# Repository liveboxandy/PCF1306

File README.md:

# PCF1306 LBA Version
PCF1306 Replacement KiCAD Project

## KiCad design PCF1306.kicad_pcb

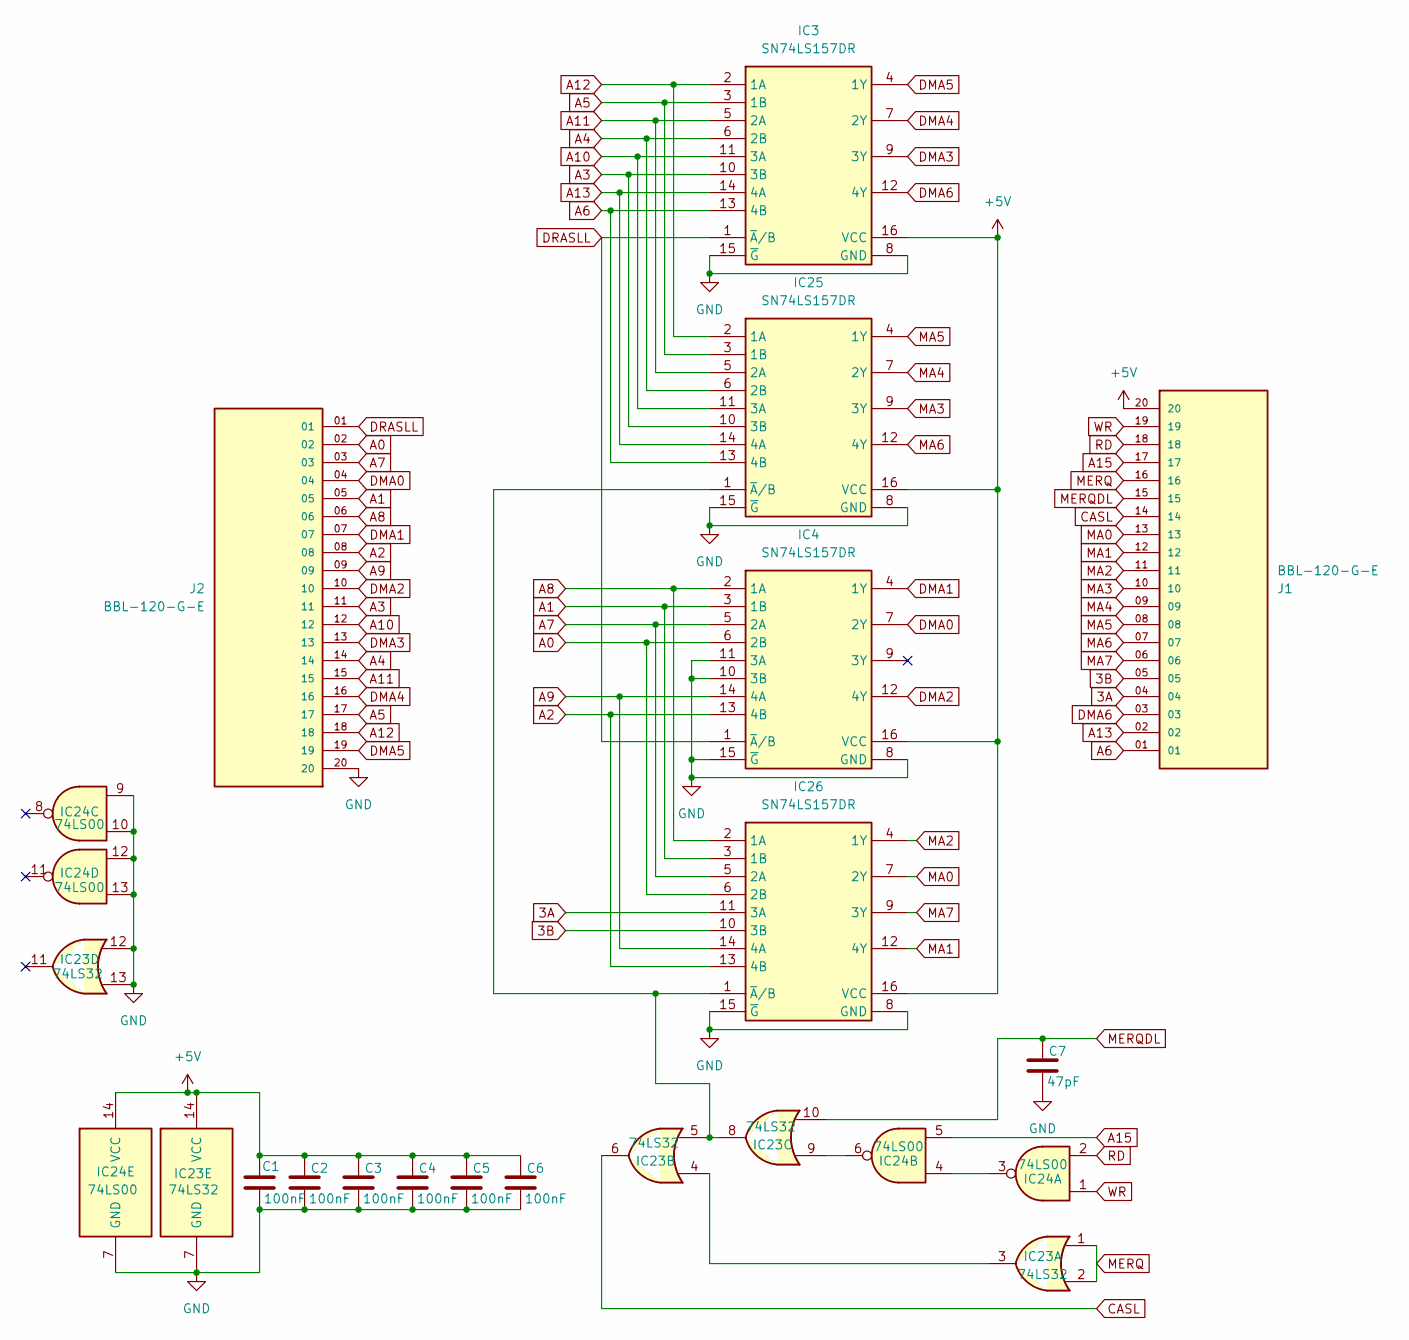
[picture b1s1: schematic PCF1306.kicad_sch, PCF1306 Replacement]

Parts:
C1, C2, C3, C4, C5, C6: 100nF; C_0805_2012Metric
C7: 47pF; C_0805_2012Metric
IC3, IC4, IC25, IC26: SN74LS157DR; SOIC127P600X175-16N; Mouser Part Number 595-SN74LS157DR
IC23: 74LS32; SOIC127P600X175-14N
IC24: 74LS00; SOIC127P600X175-14N
J1, J2: BBL-120-G-E; SAMTEC_BBL-120-G-E; PARTREV R

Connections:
3A: IC26.11 (3A), J1.04
3B: IC26.10 (3B), J1.05
+5V: C1.1, C2.1, C3.1, C4.1, C5.1, C6.1, IC3.16 (VCC), IC4.16 (VCC), IC23.14 (VCC), IC24.14 (VCC), IC25.16 (VCC), IC26.16 (VCC), J1.20
A0: IC4.6 (2B), IC26.6 (2B), J2.02
A1: IC4.3 (1B), IC26.3 (1B), J2.05
A2: IC4.13 (4B), IC26.13 (4B), J2.08
A3: IC3.10 (3B), IC25.10 (3B), J2.11
A4: IC3.6 (2B), IC25.6 (2B), J2.14
A5: IC3.3 (1B), IC25.3 (1B), J2.17
A6: IC3.13 (4B), IC25.13 (4B), J1.01
A7: IC4.5 (2A), IC26.5 (2A), J2.03
A8: IC4.2 (1A), IC26.2 (1A), J2.06
A9: IC4.14 (4A), IC26.14 (4A), J2.09
A10: IC3.11 (3A), IC25.11 (3A), J2.12
A11: IC3.5 (2A), IC25.5 (2A), J2.15
A12: IC3.2 (1A), IC25.2 (1A), J2.18
A13: IC3.14 (4A), IC25.14 (4A), J1.02
A15: IC24.5, J1.17
CASL: IC23.6, J1.14
DMA0: IC4.7 (2Y), J2.04
DMA1: IC4.4 (1Y), J2.07
DMA2: IC4.12 (4Y), J2.10
DMA3: IC3.9 (3Y), J2.13
DMA4: IC3.7 (2Y), J2.16
DMA5: IC3.4 (1Y), J2.19
DMA6: IC3.12 (4Y), J1.03
DRASLL: IC3.1 (~A/B), IC4.1 (~A/B), J2.01
GND: C1.2, C2.2, C3.2, C4.2, C5.2, C6.2, C7.2, IC3.8 (GND), IC3.15 (~G), IC4.8 (GND), IC4.10 (3B), IC4.11 (3A), IC4.15 (~G), IC23.7 (GND), IC23.12, IC23.13, IC24.7 (GND), IC24.9, IC24.10, IC24.12, IC24.13, IC25.8 (GND), IC25.15 (~G), IC26.8 (GND), IC26.15 (~G), J2.20
MA0: IC26.7 (2Y), J1.13
MA1: IC26.12 (4Y), J1.12
MA2: IC26.4 (1Y), J1.11
MA3: IC25.9 (3Y), J1.10
MA4: IC25.7 (2Y), J1.09
MA5: IC25.4 (1Y), J1.08
MA6: IC25.12 (4Y), J1.07
MA7: IC26.9 (3Y), J1.06
MERQ: IC23.1, IC23.2, J1.16
MERQDL: C7.1, IC23.10, J1.15
unnamed: IC23.3, IC23.4
unnamed: IC23.9, IC24.6
unnamed: IC24.3, IC24.4
unnamed: IC23.5, IC23.8, IC25.1 (~A/B), IC26.1 (~A/B)
RD: IC24.2, J1.18
WR: IC24.1, J1.19

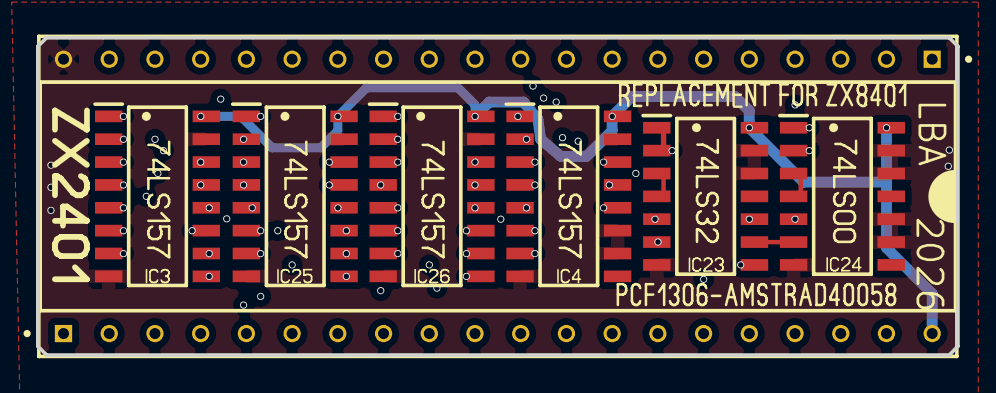
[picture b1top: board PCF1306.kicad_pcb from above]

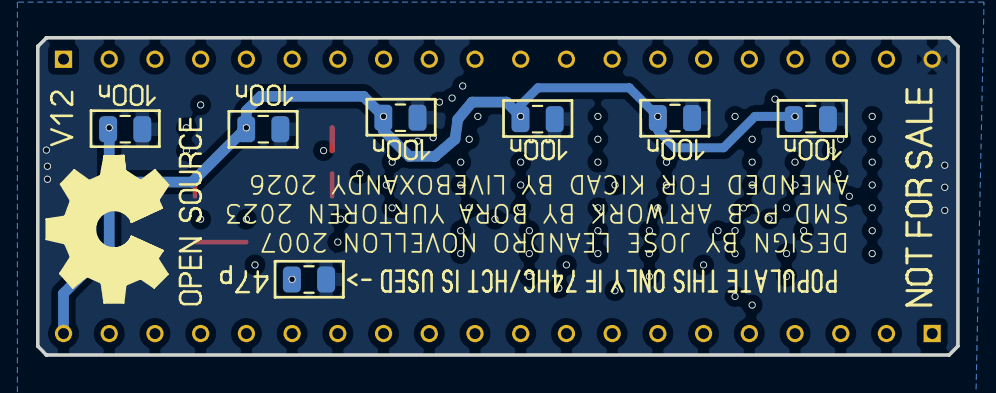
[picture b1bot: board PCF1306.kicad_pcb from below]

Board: 4 copper layers, 51.1 x 17.6 mm, 15 parts (7 on the bottom side), 44 nets.
